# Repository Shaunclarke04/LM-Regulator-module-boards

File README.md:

# LM-Regulator-module-boards

## LM78xx Regulator Module Boards v2.0

Schematics and Gerbers availabble - Original Design Files not available

## LM317 Regulator Module Board v3.0

Schematics, Gerbers and Original Design Files available
note: Voltages and Reisistor values listed are an estimate, not a garuntee of actual output voltage. Please check your output voltage with a multimeter before connecting to your circuit.

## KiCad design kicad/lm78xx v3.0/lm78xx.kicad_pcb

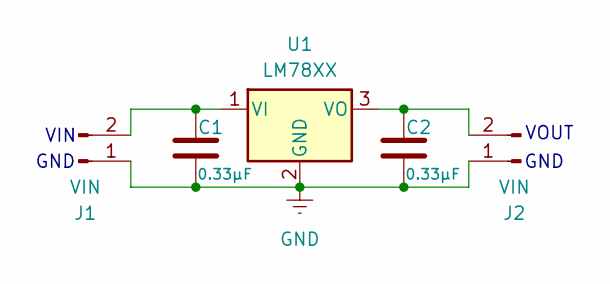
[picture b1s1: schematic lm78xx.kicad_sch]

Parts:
C1, C2: 0.33µF; C_Disc_D5.0mm_W2.5mm_P5.00mm
J1, J2: VIN; PinHeader_1x02_P2.54mm_Vertical
U1: LM78XX; TO-220-3_Horizontal_TabDown

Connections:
GND: C1.2, C2.2, J1.1, J2.1, U1.2 (GND)
unnamed: C1.1, J1.2, U1.1 (VI)
unnamed: C2.1, J2.2, U1.3 (VO)

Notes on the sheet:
GND
VIN
VOUT

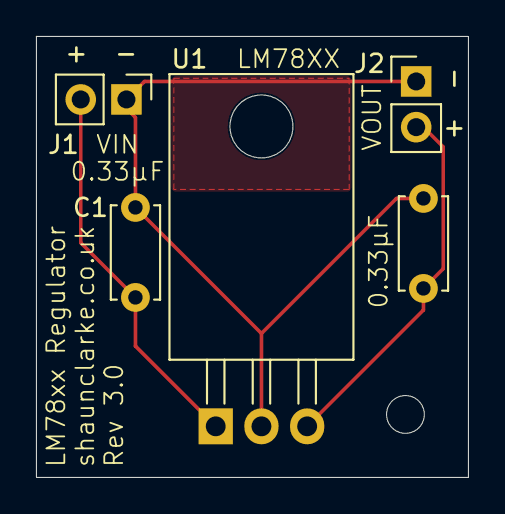
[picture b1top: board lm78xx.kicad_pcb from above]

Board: 2 copper layers, 24.0 x 24.5 mm, 5 parts (0 on the bottom side), 3 nets.

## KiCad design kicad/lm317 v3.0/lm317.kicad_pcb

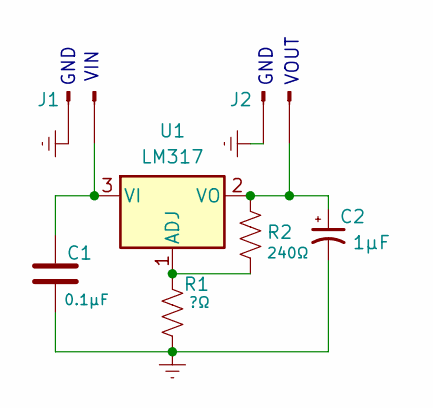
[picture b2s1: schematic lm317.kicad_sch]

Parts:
C1: 0.1µF; C_Disc_D5.0mm_W2.5mm_P5.00mm
C2: 1µF; C_Radial_D5.0mm_H11.0mm_P2.00mm
J1: VIN; PinHeader_1x02_P2.54mm_Vertical
J2: VOUT; PinHeader_1x02_P2.54mm_Vertical
R1: ?Ω; R_Axial_DIN0207_L6.3mm_D2.5mm_P7.62mm_Horizontal
R2: 240Ω; R_Axial_DIN0207_L6.3mm_D2.5mm_P7.62mm_Horizontal
U1: LM317; TO-220-3_Horizontal_TabDown

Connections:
/Earth: C1.2, C2.2, J2.1, R1.2
GND: J1.1
unnamed: C1.1, J1.2, U1.3 (VI)
unnamed: C2.1, J2.2, R2.1, U1.2 (VO)
unnamed: R1.1, R2.2, U1.1 (ADJ)

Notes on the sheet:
GND
VIN
VOUT

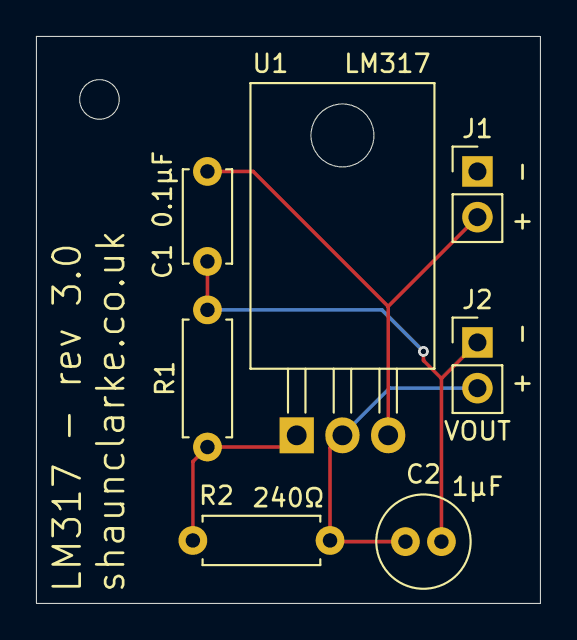
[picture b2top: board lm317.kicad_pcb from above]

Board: 2 copper layers, 28.0 x 31.5 mm, 7 parts (0 on the bottom side), 4 nets.
